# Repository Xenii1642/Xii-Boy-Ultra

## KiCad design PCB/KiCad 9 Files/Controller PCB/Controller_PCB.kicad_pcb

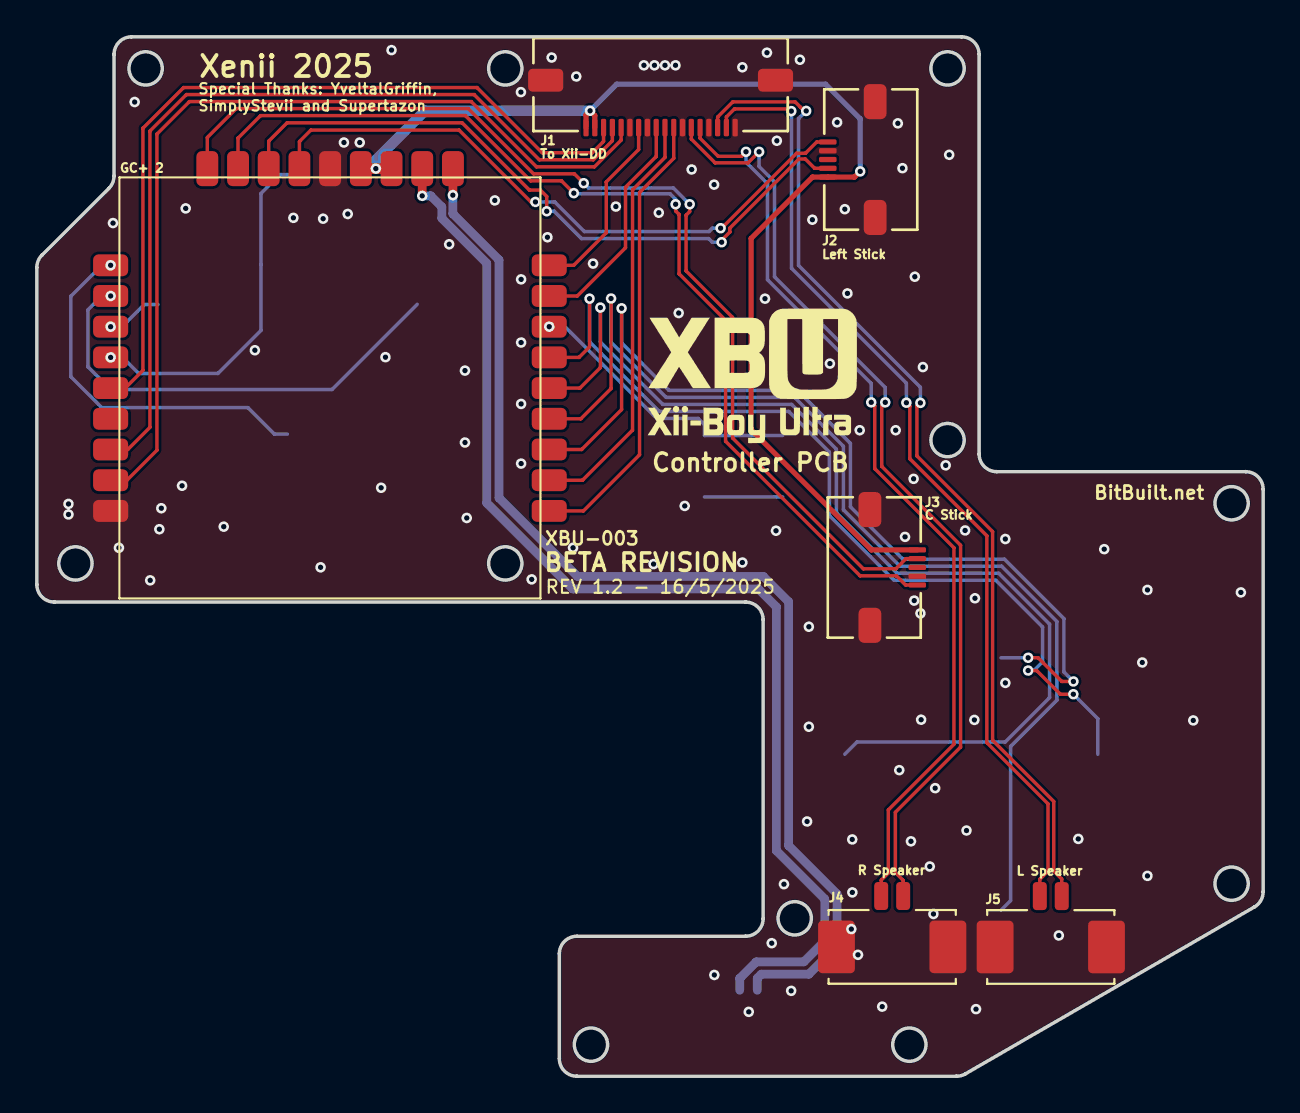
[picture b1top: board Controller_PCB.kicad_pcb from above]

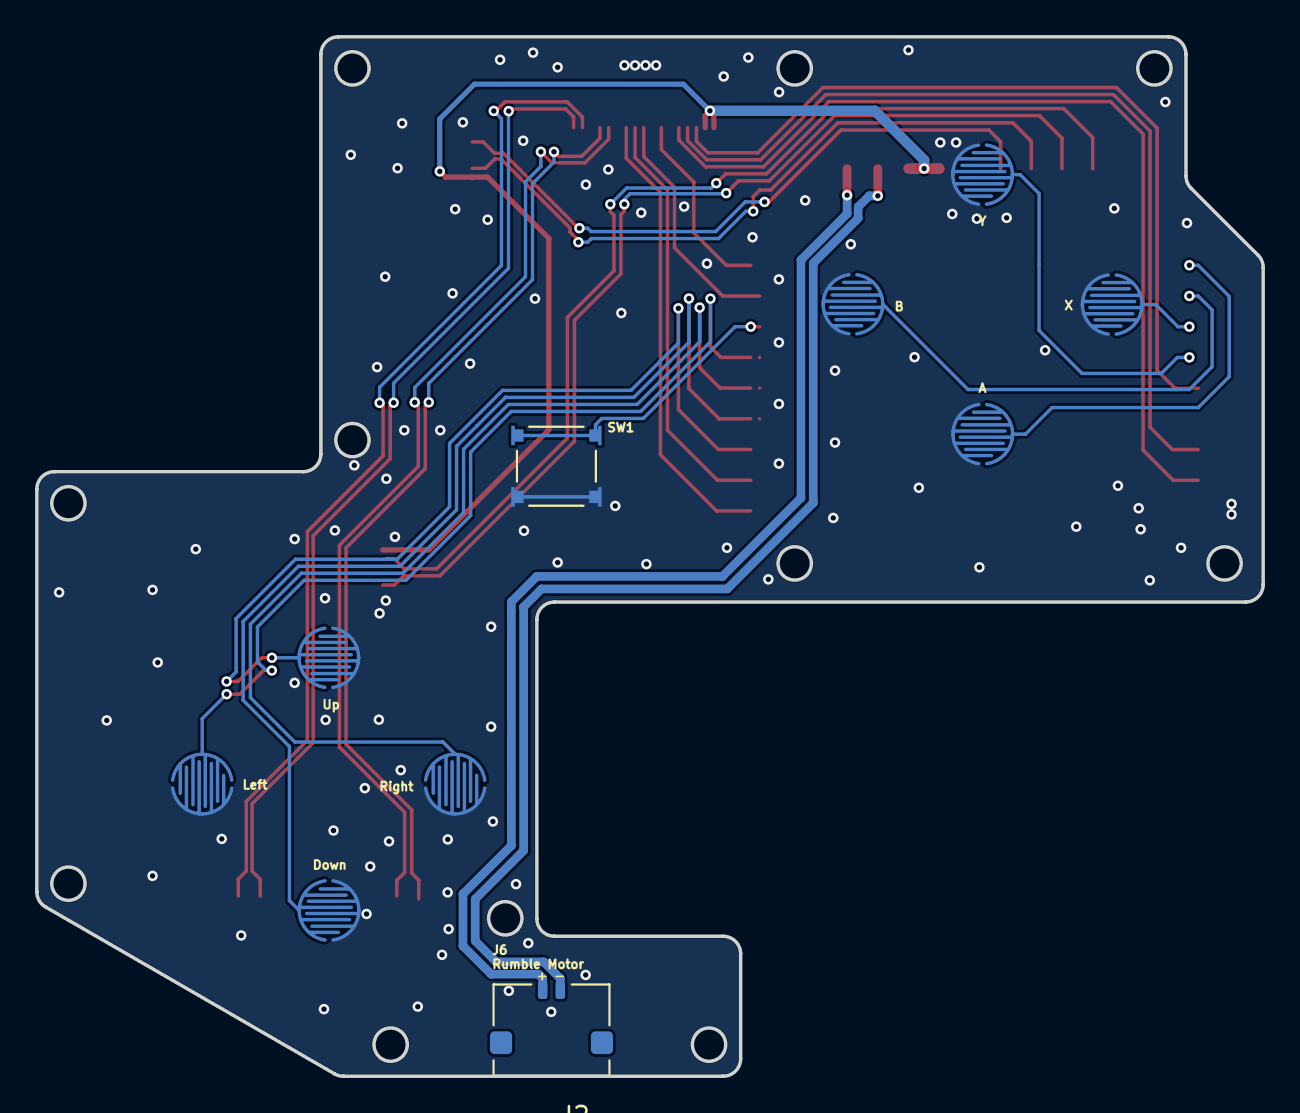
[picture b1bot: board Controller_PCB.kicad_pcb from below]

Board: 2 copper layers, 69.9 x 59.2 mm, 16 parts (10 on the bottom side), 28 nets.

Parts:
A1: DSLPad-Final
B1: DSLPad-Final
D1: DSLPad-Final
J1, J3: 0532610271; MOLEX_0532610271
J2: 5037630291; MOLEX_5037630291
J4, J5: 5051100592; CON_5051100592_MOL
J7: 5051101892; CON_5051101892_MOL
L1: DSLPad-Final
R1: DSLPad-Final
S1: SW_TL3315NF250Q
U1: GC+2.0
U2: DSLPad-Final
X1: DSLPad-Final
Y1: DSLPad-Final

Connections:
+3V3: J4.1, J5.1, J7.17, J7.18, U1.10 (3.3v), U1.23 (MP)
/A: A1.2, U1.1 (A)
/B: B1.2, U1.2 (B)
/CX: J5.5, U1.26 (CX)
/CY: J5.2, U1.27 (CY)
/DATA: J7.12, U1.20 (D)
/DD: D1.2, U1.15 (DD)
/DL: L1.2, U1.17 (DL)
/DR: R1.2, U1.16 (DR)
/DU: U1.14 (DU), U2.2
/L: J7.8, U1.12 (L)
/L+: J1.2, J7.3
/L-: J1.1, J7.2
/LT: J7.9, U1.13 (LT)
/LZ: J7.10, U1.19 (Z2)
/M+: J2.2, U1.22 (M+)
/M-: J2.1, U1.21 (M-)
/R: J7.14, U1.8 (R)
/R+: J3.2, J7.6
/R-: J3.1, J7.5
/RT: J7.15, U1.7 (RT)
/RZ: J7.16, U1.5 (Z)
/START: S1.3, S1.4, U1.18 (S)
/SX: J4.5, U1.24 (SX)
/SY: J4.2, U1.25 (SY)
/X: U1.3 (X), X1.2
/Y: U1.4 (Y), Y1.2
GND: A1.1, B1.1, D1.1, J1.S1 (SHIELD), J1.S2 (SHIELD__1), J3.S1 (SHIELD), J3.S2 (SHIELD__1), J4.4, J4.P1, J4.P2, J5.4, J5.P1, J5.P2, J7.1, J7.4, J7.7, J7.11, J7.13, J7.P1, J7.P2, L1.1, R1.1, S1.1, S1.2, U1.9 (GND), U2.1, X1.1, Y1.1
